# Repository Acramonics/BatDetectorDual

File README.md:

Dual Bat Detector
=================

Andrew Martin, acramonics, 2026
-------------------------------

This design combines two circuits for bat detection that use different
principles.

### Frequency Divider

The top part of the circuit diagram and PCB uses two LM386 audio
amplifiers to boost the signal and a 4024 chip to divide the frequency
down to the audio range. This circuit is the 'Enhanced Bat Detector'
from https://batdetector.freevar.com/ This design doesn't require any
tuning of the detector and will cover all frequencies.

### Heterodyne

This bottom part of the circuit diagram and PCB implements a
heterodyne design with the same principle as an AM radio. The circuit
comes from *Nuts and Volts* magazine at
https://www.nutsvolts.com/magazine/article/june2011_berber This uses
just one IC (an LM324 quad opamp). The first opamp is a high-gain
amplifier combined with a high-pass filter (>20kHz); the second opamp
provides further amplification and filtering; the third opamp is an
oscillator with a frequency range of around 15-110kHz; the fourth
opamp is the heterodyne mixer taking the amplified/filtered signal
together with the oscillator signal and outputs the difference between
them.

Building the circuit
--------------------

You can, of course just build one part of the circuit, but the design
is such that you can use a 3PDT switch to select between the two
circuits. (You could also use a 3P3T switch to have an off position
where nothing is connected.)

### Switches

- An ON-OFF-ON toggle switch, the MTS-303R is available from
  [AliExpress](https://www.aliexpress.com/item/1005007484491572.html)
- A 3PDT toggle switch, the TE Connectivity 2-1825139-3, is available
  from
  [Rapid Electronics](https://www.rapidonline.com/te-connectivity-2-1825139-3-toggle-switch-3pdt-on-off-on-pcb-mount-15-1926)
- Alpha produce 4P3T rotary switches such as the SR2611-0403-38F5
  available from
  [Rapid Electronics](https://www.rapidonline.com/taiwan-alpha-sr2611-0403-38f5-make-before-break-rotary-switch-4-pole-3-way-79-0115)
  or the SR2511F-0303-19R0B-E9-S-W-159 available from
  [Mouser](https://www.mouser.co.uk/ProductDetail/Alpha-Taiwan/SR2511F-0303-19R0B-E9-S-W-159?qs=8%252Br4Hz5Xir%2F8i45vdtZdhg%3D%3D)
- Other choices include 4P3T switches from Alps Alpine
  [RS, SRRM433700](https://uk.rs-online.com/web/p/rotary-switches/1239626)
  and various choices from Lorlin CK  
  [See the datasheet](https://docs.rs-online.com/7602/A700000008016972.pdf)
- A 4P3T rotary switch, the RS26, is also available from AliExpress
  https://www.aliexpress.com/item/1005008776212710.html
- Various 3P3T wafer-style switches are also available and described
  as 'Rotary Band Switches' See:
  - https://www.aliexpress.com/item/1005011839909128.html
  - https://www.aliexpress.com/item/1005007021912980.html
  - https://www.aliexpress.com/item/1005005723913772.html
  - https://www.aliexpress.com/item/1005011597813751.html
  - https://www.aliexpress.com/item/1005006184759913.html
  - https://www.aliexpress.com/item/1005010336131768.html
  - https://www.aliexpress.com/item/1005008856647634.html

### Potentiometer

The dual-gang B100K potentiometer is a compromise between the
recommended B50K for the heterodyne circuit and the A220K for the
frequency divider. It should be fine for the latter, but it may be
necessary to put a 47K resistor in parallel with the pot used for the
heterodyne circuit.

### Optional parts

R2, R3, C5 and C10 in the frequency divider circuit shouldn't be
needed but can be added if there is instability in the
amplifier.  Similarly, C3 and C8 shouldn't be needed.

L1 and L2 may not be needed depending on the transducer/microphone used.

### Transducer/Microphone

40kHz ultrasonic transducer are easily available from AliExpress and
most good component suppliers. However, according to the *Nuts and
Volts* article, a simple piezo or ceramic sounder used as a microphone
can be better. produce superior results. For these, L1 and L2 are not
needed. 

### Headphones/earpiece

A crystal earpiece is ideal.

### Component values

Some of the values are dependent on the sensor/microphone used.

**With a 40kHz ultrasonic transducer:**

- L1=6.8mH
- R1=150R or 220R
- RV1 should be set to a value in the range 150R to 2K2. 470R to 1K5
  is a good starting point. Increased values can be used if the
  detector is too noisy or oscillates.
- L2 is in the range 10uH to 6.8mH

**With other piezo/ceramic transducers**

- L1/L2 are not used
- R1 and RV1 adjusted as above

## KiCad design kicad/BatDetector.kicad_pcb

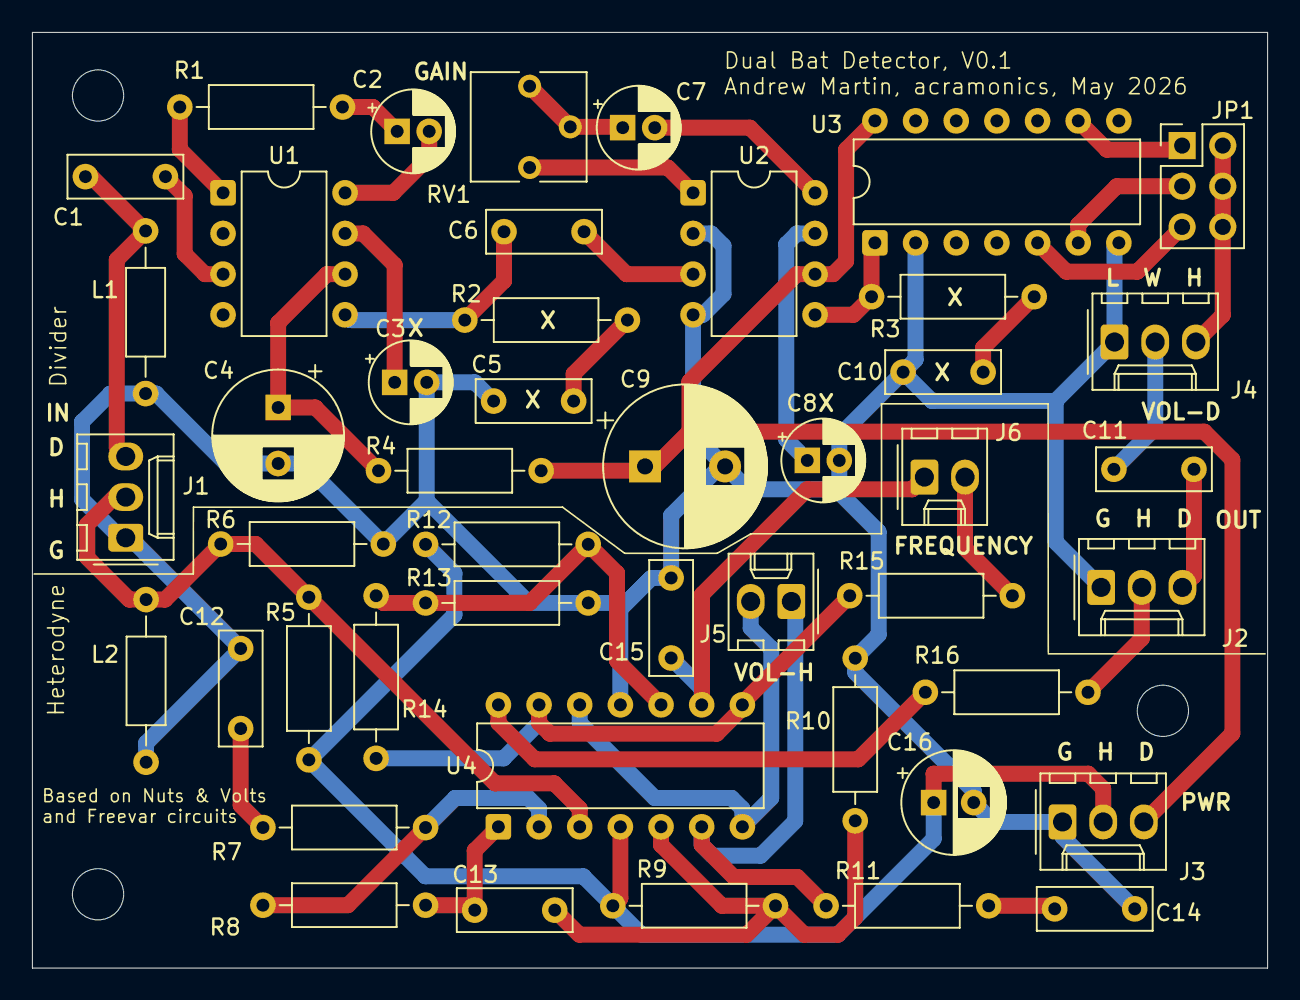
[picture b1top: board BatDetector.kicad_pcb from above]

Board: 2 copper layers, 77.2 x 58.5 mm, 46 parts (0 on the bottom side), 39 nets.

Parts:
C1, C11: 22nF; C_Rect_L7.0mm_W2.5mm_P5.00mm
C2, C7: 10uF; CP_Radial_D5.0mm_P2.00mm
C3, C8: *10uF; CP_Radial_D5.0mm_P2.00mm
C4: 220uF; CP_Radial_D8.0mm_P3.50mm
C5, C10: *Inf; C_Rect_L7.0mm_W2.5mm_P5.00mm
C6: 47nF; C_Rect_L7.0mm_W2.5mm_P5.00mm
C9: 470uF; CP_Radial_D10.0mm_P5.00mm
C12, C14: 1nF; C_Rect_L7.0mm_W2.5mm_P5.00mm
C13: 100nF; C_Rect_L7.0mm_W2.5mm_P5.00mm
C15: 470pF; C_Rect_L7.0mm_W2.5mm_P5.00mm
C16: 47uF; CP_Radial_D6.3mm_P2.50mm
J1, J2, J3, J4: Conn_01x03_Pin; Molex_KK-254_AE-6410-03A_1x03_P2.54mm_Vertical
J5, J6: Conn_01x02_Pin; Molex_KK-254_AE-6410-02A_1x02_P2.54mm_Vertical
JP1: Conn_02x03_Odd_Even; PinHeader_2x03_P2.54mm_Vertical
L1: +6.8mH; L_Axial_L5.3mm_D2.2mm_P10.16mm_Horizontal_Vishay_IM-1
L2: *10uH; L_Axial_L5.3mm_D2.2mm_P10.16mm_Horizontal_Vishay_IM-1
R1: +150R; R_Axial_DIN0207_L6.3mm_D2.5mm_P10.16mm_Horizontal
R2, R3: *Inf; R_Axial_DIN0207_L6.3mm_D2.5mm_P10.16mm_Horizontal
R4: 220R; R_Axial_DIN0207_L6.3mm_D2.5mm_P10.16mm_Horizontal
R5, R6, R8, R9, R10: 1M; R_Axial_DIN0207_L6.3mm_D2.5mm_P10.16mm_Horizontal
R7: 470R; R_Axial_DIN0207_L6.3mm_D2.5mm_P10.16mm_Horizontal
R11: 1K; R_Axial_DIN0207_L6.3mm_D2.5mm_P10.16mm_Horizontal
R12, R13, R14: 220k; R_Axial_DIN0207_L6.3mm_D2.5mm_P10.16mm_Horizontal
R15: 1k; R_Axial_DIN0207_L6.3mm_D2.5mm_P10.16mm_Horizontal
R16: 240R; R_Axial_DIN0207_L6.3mm_D2.5mm_P10.16mm_Horizontal
RV1: 5K; Potentiometer_Vishay_T73YP_Vertical
U1, U2: LM386; DIP-8_W7.62mm
U3: 4024; DIP-14_W7.62mm
U4: LM324; DIP-14_W7.62mm

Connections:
+9V: C9.1, J3.3, R4.2, U2.6 (V+), U3.14 (VDD)
+9VA: C16.1, J3.2, R5.1, R9.2, R12.1, U4.4 (V+)
GND: C3.2, C4.2, C5.1, C8.2, C9.2, C10.1, C12.2, C14.1, C15.1, C16.2, J1.1, J2.1, J3.1, J4.1, L1.2, L2.2, R6.2, R10.1, R13.2, U1.2 (-), U1.4 (GND), U2.2 (-), U2.4 (GND), U3.2 (MR), U3.7 (VSS), U4.11 (V-)
IN1: C1.1, J1.3, L1.1
IN2: J1.2, L2.1, R5.2, R6.1, U4.3 (+)
unnamed: C2.1, R1.1
unnamed: C2.2, U1.8 (GAIN)
unnamed: C5.2, R2.2
unnamed: C6.1, R2.1, U1.5
unnamed: C7.1, RV1.2, RV1.3
unnamed: C7.2, U2.8 (GAIN)
unnamed: C10.2, R3.2
unnamed: C12.1, R7.2
unnamed: C13.1, R8.2, U4.1
unnamed: C14.2, R11.1
unnamed: C11.2, J4.2
unnamed: J4.3, JP1.2, JP1.4, JP1.6
unnamed: J5.1, R11.2, U4.6 (-)
unnamed: J5.2, U4.7, U4.12 (+)
unnamed: C15.2, J6.1, U4.9 (-)
unnamed: J6.2, R15.2
unnamed: JP1.1, U3.9 (Q2)
unnamed: JP1.3, U3.6 (Q3)
unnamed: JP1.5, U3.5 (Q4)
unnamed: R1.2, U1.1 (GAIN)
unnamed: R16.2, U4.14
unnamed: RV1.1, U2.1 (GAIN)
unnamed: C1.2, U1.3 (+)
unnamed: C3.1, U1.7 (BYPASS)
unnamed: C4.1, R4.1, U1.6 (V+)
unnamed: C6.2, U2.3 (+)
unnamed: C8.1, U2.7 (BYPASS)
unnamed: R3.1, U2.5, U3.1 (~CLK)
unnamed: R7.1, R8.1, U4.2 (-)
unnamed: C13.2, R9.1, R10.2, U4.5 (+)
unnamed: R12.2, R13.1, R14.1, U4.10 (+)
unnamed: R14.2, R15.1, U4.8, U4.13 (-)
OUT1: C11.1, J2.3
OUT2: J2.2, R16.1

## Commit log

2026-05-21 Some layout tweaks
2026-05-21 Added README
2026-05-21 Regenerated gerbers
2026-05-26 Added BOM
2026-06-23 Added BOM pdf
